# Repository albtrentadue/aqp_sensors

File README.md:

# aqp_sensors
Software components for the Aquaponic project

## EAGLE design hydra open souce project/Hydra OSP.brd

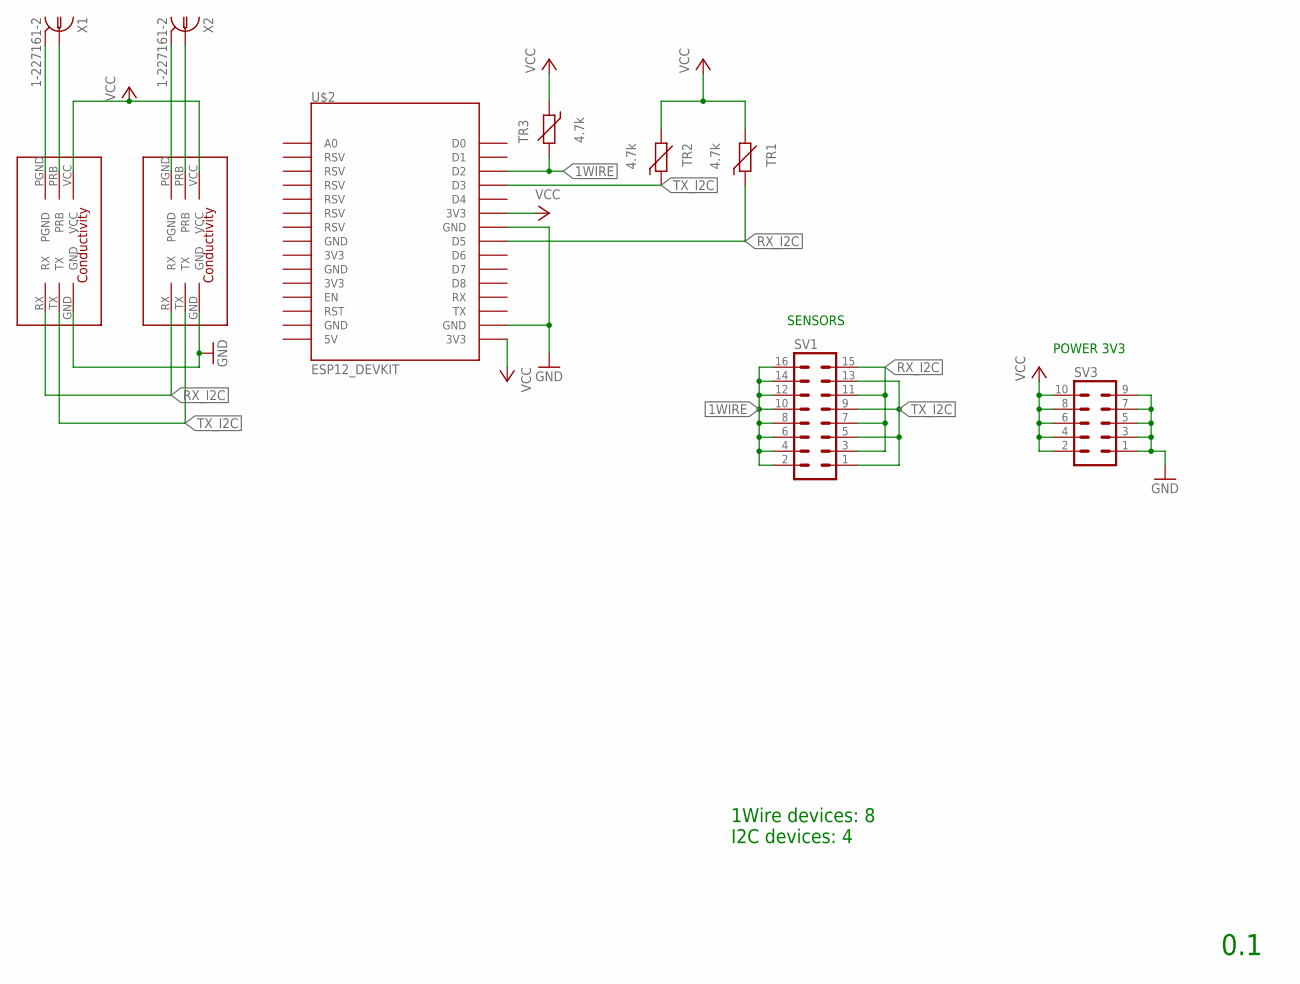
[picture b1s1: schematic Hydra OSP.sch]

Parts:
SV1: MA08-2
SV3: MA05-2
TR1, TR2, TR3: 4.7k; R-5
U$1, U$3: ATLSCI_COND; ATLAS_SCI_COND
U$2: ESP12_DEVKIT
X1, X2: 1-227161-2; AMP_227161

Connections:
1WIRE: SV1.2, SV1.4, SV1.6, SV1.8, SV1.10, SV1.12, SV1.14, SV1.16, TR3.2, U$2.D2
GND: SV3.1, SV3.3, SV3.5, SV3.7, SV3.9, U$1.GND, U$2.GND@2 (GND), U$2.GND@3 (GND), U$3.GND
unnamed: U$1.PGND, X1.2
unnamed: U$1.PRB, X1.1
unnamed: U$3.PRB, X2.1
unnamed: U$3.PGND, X2.2
RX_I2C: SV1.3, SV1.7, SV1.11, SV1.15, TR1.1, U$1.RX, U$2.D5, U$3.RX
TX_I2C: SV1.1, SV1.5, SV1.9, SV1.13, TR2.1, U$1.TX, U$2.D3, U$3.TX
VCC: SV3.2, SV3.4, SV3.6, SV3.8, SV3.10, TR1.2, TR2.2, TR3.1, U$1.VCC, U$2.3V3@1 (3V3), U$2.3V3@2 (3V3), U$3.VCC

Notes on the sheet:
1Wire devices: 8 I2C devices: 4
0.1
POWER 3V3
SENSORS

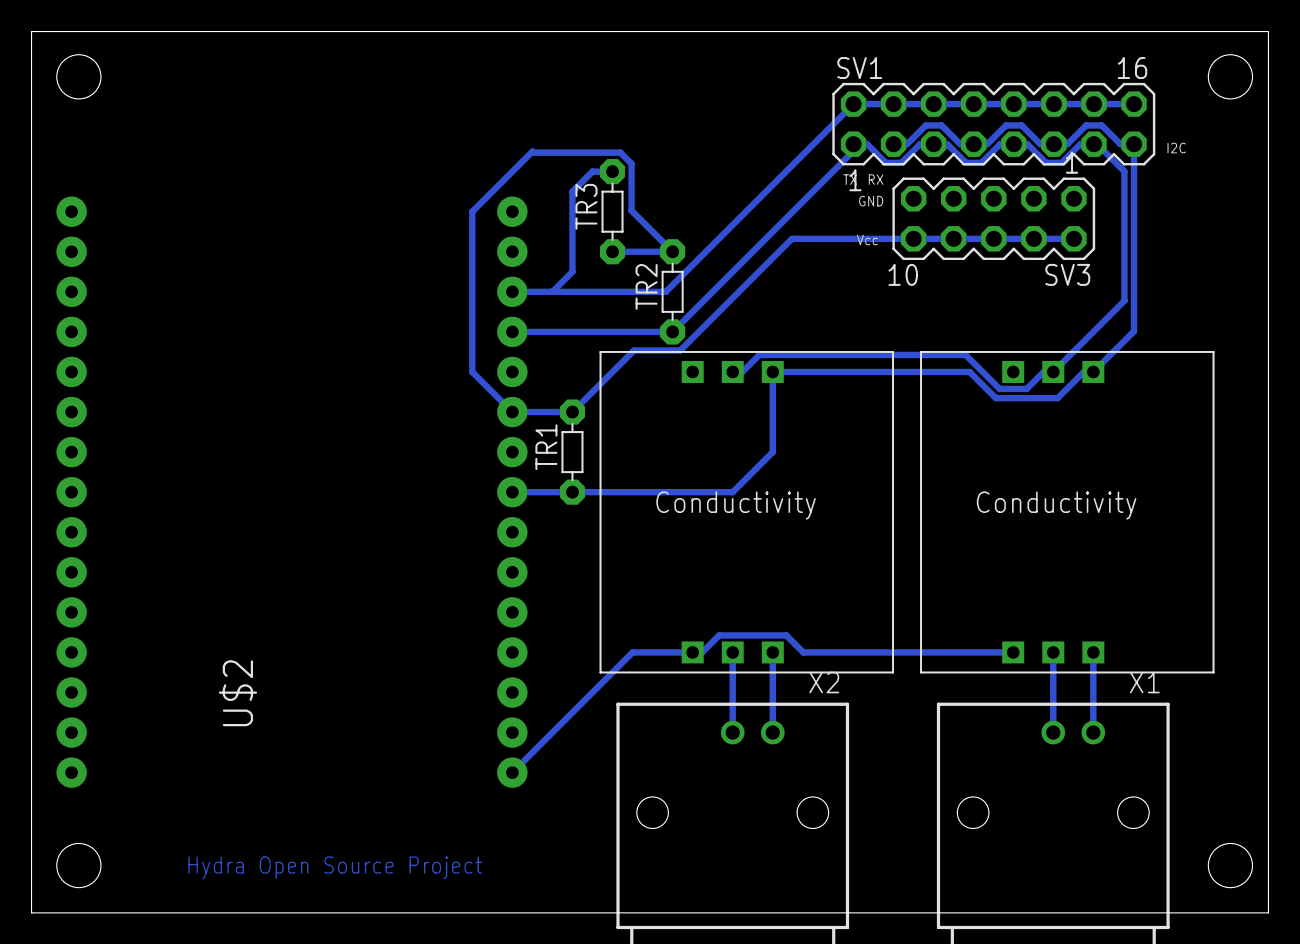
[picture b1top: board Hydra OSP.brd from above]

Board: 1 copper layer, 78.4 x 55.9 mm, 10 parts (0 on the bottom side), 9 nets.

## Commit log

2016-10-19 primo commit!
2016-10-19 mqtt_wifi added
    DHT11, oled e Mqtt
2016-10-21 Reorganized for MQTT/WiFi usage
2016-10-31 Version 0.1
    added: wifi, MQTT client, DHT11 and display. We need to talk about
    “void make_messanger” and “send_messanger”.
2016-11-02 dht11's library easy
2016-11-02 Delete dht11.zip
    Removed altered file
2016-11-02 Ready for test with MQTT WiFi and DHT11
2016-11-20 aqp_sensors adafruit
    This example is made for Adafruit IO and Adafruit MQTT library
2016-11-30 fritzing schematic
    Version 0.1
2016-11-30 fritzing schematic
2016-12-12 V0.1 stable
    This version works.
2016-12-12 update
    added FEEDS: dht_temperature & dht_humidity. The code works.
2016-12-20 Added feeds
2016-12-21 ORP data
    Added ORT example code and documentation
2016-12-21 ORT data sheet
2016-12-21 new files for oxy I2C
2016-12-21 Added Arduino sample sketch
2016-12-25 ORP_i2c doc & sketch working
    Added doc for ORP_i2c sensor & sketch for ESP works and publish
2017-01-02 Changed structure on master branch to match the OXY branch
2017-01-02 Modified file structure to match the master
2017-01-07 removed duplicated file
2017-01-18 Average of measures + time interval sends + reorder code
2017-01-21 Code reorganized and tested with both DO and ORP sensor cards
2017-01-22 Modified ATS sensor interface functions to handle more commands
2017-01-25 Fixed ATS sensor reading problem
2017-01-31 BreadBoard
2017-01-31 Committed code for test and calibration
2017-01-31 Oled support added
2017-02-01 Schematic V0.2
2017-02-06 Fixed negative ORP value bug
2017-02-12 added new schematic, DHT22 and DS18B20
    DHT22 with one wire and DS18B20 with your own library
2017-02-13 Added pH and Oxy correction and integration tests
2017-02-15 Added Oled at breadBoard and code
2017-02-20 added multi wifi profiles and No Wifi choice
    You can create an Hotspot on your Android phone with:
    - name: AQP
    - pass: ca5ac0r51n1
2017-03-04 clean the schematics
2017-03-06 Removed unused arduino sketches
2017-04-05 macro serial print test
2017-04-05 PCB and schematic
2017-04-27 DRC eurocircuits
2017-04-30 PCB ready for eurocircuits
2018-01-12 WiFi Manager added
    Not tested on board
